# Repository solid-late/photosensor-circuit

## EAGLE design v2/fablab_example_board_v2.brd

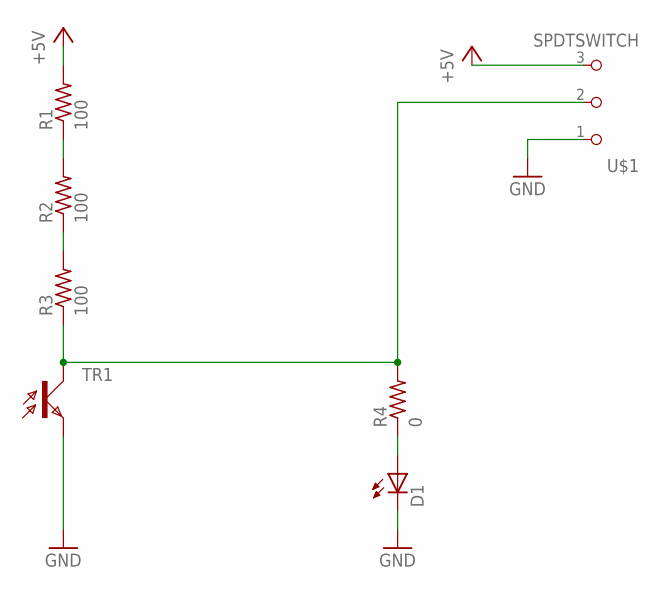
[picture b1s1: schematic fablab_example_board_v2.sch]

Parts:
D1: LEDFAB1206; LED1206FAB
R1, R2, R3: 100; R1206FAB
R4: 0; R1206FAB
TR1: PHOTOTRANSISTOR-NPN1206; OP1206
U$1: SPDTSWITCH

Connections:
+5V: R1.2, U$1.3
GND: D1.2 (C), TR1.E, U$1.1
unnamed: R2.1, R3.2
unnamed: R1.1, R2.2
unnamed: R3.1, R4.2, TR1.C, U$1.2
unnamed: D1.1 (A), R4.1

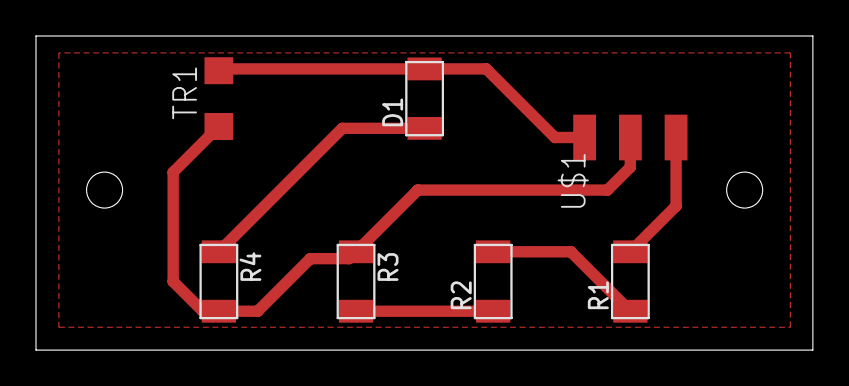
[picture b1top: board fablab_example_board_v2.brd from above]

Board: 2 copper layers, 43.2 x 17.4 mm, 7 parts (0 on the bottom side), 6 nets.
